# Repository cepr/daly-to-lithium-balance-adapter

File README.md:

# Energica Ego (2018) — Replacement Battery BMS Interface

Replacement traction battery for a 2018 Energica Ego. The original Lithium Balance s-BMS
master (BMCU) stays in the bike. The original cell-monitoring slave boards are gone, and a
small microcontroller board takes their place.

## Battery

| Item | Value |
|---|---|
| Chemistry | NMC |
| Modules | 4, connected in series |
| Cells per module | 20 in series |
| Total | **80S** |

## System overview

- **BMS master:** Lithium Balance s-BMS **BMCU** board (firmware 6.18.0, PIC18F4680).
- **Original slaves (LMUs):** 10 Lithium Balance cell-monitor boards with 8 cells each
  (10 × 8 = 80 cells). They are no longer available.
- **Replacement:** 4 **DALY Smart Active Balancers**: three 24S (the largest model) and one
  20S for the top module. They balance the cells and measure every cell voltage.
- **Interface board:** a microcontroller that reads the cell voltages from the 4 DALY
  balancers and answers the BMCU's slave-bus requests as if it were the 10 original LMUs.
  The BMCU keeps running its stock firmware and sees no difference.

### Balancer wiring and module overlap

A balancer covering only one module could balance cells within that module but not move
energy between modules. Balancers #1–#3 are therefore 24S: 20 channels on their own module and
4 on the next module up. A balancer that spans a module boundary moves charge across that
boundary, so all 4 modules are pulled to the same level. Module 4 is at the top of the pack and
has no next module, so balancer #4 is a 20S unit on module 4 only. The module 3/4 boundary is
bridged by balancer #3.

```
 Global cell       1–20     |    21–40    |    41–60    |    61–80
 Module          Module 1   |  Module 2   |  Module 3   |  Module 4
 Balancer #1   [  ch 1–20  ] [21–24]
 Balancer #2                 [  ch 1–20  ] [21–24]
 Balancer #3                               [  ch 1–20  ] [21–24]
 Balancer #4                                             [  ch 1–20  ]
```

| Balancer | Model | Channels 1–20 | Channels 21–24 (overlap) | Global cells |
|---|---|---|---|---|
| #1 | 24S | Module 1, cells 1–20 | Module 2, cells 1–4 | 1–24 |
| #2 | 24S | Module 2, cells 1–20 | Module 3, cells 1–4 | 21–44 |
| #3 | 24S | Module 3, cells 1–20 | Module 4, cells 1–4 | 41–64 |
| #4 | 20S | Module 4, cells 1–20 | — | 61–80 |

### Cell mapping

The BMCU numbers cells by slave: global cell = (slave − 1) × 8 + index + 1. Each cell is
read from the balancer that owns its module (the **primary** reading). Cells in an overlap
zone are measured by a second balancer too: each time the BMCU reads an LMU's cells, its
overlap cells switch between the two readings, so the BMCU and the diagnostic software see
both. The switch happens after the BMCU's temperature read, so the cells and temperatures of
one scan always come from the same balancer (primary first). A sense-wire or balancer fault shows as a cell whose value jumps between reads. A
missing reading is reported as a cell fault on its turn, even when the other one is valid.

| LMU (slave addr) | Global cells | Primary reading | Second reading |
|---|---|---|---|
| 1 | 1–8 | #1 ch 1–8 | — |
| 2 | 9–16 | #1 ch 9–16 | — |
| 3 | 17–24 | #1 ch 17–20 + #2 ch 1–4 | cells 21–24: #1 ch 21–24 |
| 4 | 25–32 | #2 ch 5–12 | — |
| 5 | 33–40 | #2 ch 13–20 | — |
| 6 | 41–48 | #3 ch 1–8 | cells 41–44: #2 ch 21–24 |
| 7 | 49–56 | #3 ch 9–16 | — |
| 8 | 57–64 | #3 ch 17–20 + #4 ch 1–4 | cells 61–64: #3 ch 21–24 |
| 9 | 65–72 | #4 ch 5–12 | — |
| 10 | 73–80 | #4 ch 13–20 | — |

### Temperature mapping

The interface board has 4 NTC inputs, one per module (T1 = module 1 … T4 = module 4), and each
DALY balancer reports its PCB temperature (balancer #n sits on module n). Each LMU fills its
four temperature registers like a real LMU (protocol doc §7.2):

| Register | Real LMU | Interface board |
|---|---|---|
| `0x7E5` | Pcb 1 | Balancer PCB temperature (DALY register `0x0020`) |
| `0x7E6` | Pcb 2 | Not fitted (`0x7A`) |
| `0x7E7` | Bat 1, NTC on L-J2 | Module NTC |
| `0x7E8` | Bat 2, optional NTC on L-J6 | Not fitted (`0x7A`) |

The BMCU ignores "not fitted" and uses the other two for its min/max/average. LMUs 3 and 8 span
a module boundary: like the overlap cells, each time the BMCU reads their temperatures they
switch between the two modules' values, in step with the overlap cells: upper module (#2 / #4,
the overlap cells' primary balancer) first, then the lower one. A fault shows on its own turn.

| LMU | Module(s) | Bat 1 (`0x7E7`) | Pcb 1 (`0x7E5`) |
|---|---|---|---|
| 1, 2 | 1 | T1 | Balancer #1 |
| 3 | 1 + 2 | T1, T2 in turn | #1, #2 in turn |
| 4, 5 | 2 | T2 | #2 |
| 6, 7 | 3 | T3 | #3 |
| 8 | 3 + 4 | T3, T4 in turn | #3, #4 in turn |
| 9, 10 | 4 | T4 | #4 |

A balancer that hasn't answered for 5 s reports its PCB sensor as open (`0xD7`), on top of
the cell faults.

Value coding (see [s-BMS protocol §7.2](LithiumBalance_sBMS_RS485_Protocol.md)):

- Valid readings are clamped to −40 … +120 °C, so they never collide with the special codes.
- An open sensor (ADC near full scale) reports `0xD7` (low-side fault). A shorted sensor (ADC near
  0) reports `0x79` (high-side fault). Every LMU that uses that sensor reports the fault.
- LMUs 3 and 8 report a fault if either of their two sensors is faulty, so a broken sensor
  can't be hidden by the average.

## Repository contents

| Path | Description |
|---|---|
| [`LithiumBalance_sBMS_RS485_Protocol.md`](LithiumBalance_sBMS_RS485_Protocol.md) | BMCU ↔ slave-board RS485 protocol, reverse-engineered from the BMCU firmware: framing, CRC, addressing, start-up enumeration, cyclic polling, register map, value coding. |
| [`DALY_Active_Balancer_UART_Protocol.md`](DALY_Active_Balancer_UART_Protocol.md) | DALY active balancer UART protocol (D2 "Modbus" framing, with the classic A5 framing as fallback), compiled from DALY documents and community work. Not yet validated on hardware; see its §8. |
| [`BMCU 6.18.0.hex`](BMCU%206.18.0.hex) | BMCU application firmware image, the source of the s-BMS protocol analysis. |
| [`pic18_dis.py`](pic18_dis.py) | Minimal PIC18 disassembler (PIC18F4680 SFR names) used to analyse the firmware: `python3 pic18_dis.py "BMCU 6.18.0.hex" > bmcu.asm` |
| [`slave_sim/`](slave_sim/) | Python/Tkinter simulator of up to 32 s-BMS slave boards, plus a BMCU emulator and tests. Use it to check the protocol against the real BMCU before the interface board exists. See [`slave_sim/README.md`](slave_sim/README.md). |
| [`can_monitor/`](can_monitor/) | Python/Tkinter Linux GUI (SocketCAN) that decodes the battery CAN messages in [`Battery_canbus_protocol.html`](Battery_canbus_protocol.html), with plotting, recording and log replay. See [`can_monitor/README.md`](can_monitor/README.md). |
| [`daly/`](daly/) | DALY balancer tooling. `fake_balancer.py` emulates a balancer (D2 protocol) on a USB-TTL adapter, for testing the firmware; see [Testing on the NUCLEO-G0B1RE](firmware/README.md#testing-on-the-nucleo-g0b1re). |
| [`docs/`](docs/) | Images used by this README (`system_overview.svg`). |
| [`hardware/interface_board/`](hardware/interface_board/) | KiCad 10 project of the interface board (draft): root sheet plus Power, MCU, BMCU (RS485), CAN, Temperatures, FANs, and one isolated balancer channel sheet used 4 times. PCB routed (first pass). Custom symbols are in `local.kicad_sym`, custom footprints in `lithium_balance.pretty` and `Molex.pretty`. |
| [`firmware/`](firmware/) | Interface board firmware in Rust (Embassy): s-BMS slave emulation, DALY polling, cell and temperature mapping. Compiles and is unit-tested on the PC; not yet run on hardware. See [`firmware/README.md`](firmware/README.md). |

## Protocol summary

| | s-BMS slave bus | DALY balancer |
|---|---|---|
| Physical | RS485, half-duplex, multi-drop | TTL UART (open-collector TX, needs pull-up) or RS485 |
| Format | 38400 baud, 8N1 | 9600 baud, 8N1 |
| Framing | ASCII hex: `CMD DEST SRC PAYLOAD CRC_H CRC_L CR` | Binary, 8-byte Modbus-like request (`0xD2` …) |
| CRC | CRC-16, poly 0xAC9A, init 0xFFFF (bytes 0x00/0x0D/0x1B bumped by 1) | CRC-16/Modbus |
| Role of the interface board | Slave (answers the BMCU) | Master (polls each balancer) |

On the s-BMS side the interface board has to:

1. Take part in the start-up enumeration. Each emulated LMU answers address `F0` in
   daisy-chain order and accepts its address `01`…`0A`.
2. Answer `q` reads of register `0x7D0` (8 cell voltages, uint16 big-endian, mV) and
   `0x7E5` (4 temperatures, int8 °C, see [Temperature mapping](#temperature-mapping)).
3. Keep the BMCU's charge counter: the BMCU writes it to registers `0x7E0`–`0x7E3` of slave 1
   every few seconds and reads it back at start-up to restore its SoC. The board must store it
   across power cycles (protocol doc §7.6).
4. Report missing or stale DALY data as a fault (for example `0x4000` for the affected cells, or no reply),
   so the BMCU's protection logic still works.
5. Build each LMU's 8 cells from the right balancer channels (see [Cell mapping](#cell-mapping)),
   and report the two readings of an overlap cell in turn.

See the two protocol documents for the details.

## Hardware

> **Status:** proposed parts, not yet prototyped. Check the datasheets and current availability before
> ordering.

### Isolation concept

Each balancer's comm port is referenced to the negative of the module it sits on, so the 4
ports are at very different potentials:

| Balancer | Port ground ≈ | Highest cell ≈ |
|---|---|---|
| #1 | 0 V | 100 V |
| #2 | 84 V | 185 V |
| #3 | 168 V | 270 V |
| #4 | 252 V | 336 V |

The interface board therefore talks to each balancer over its **TTL UART** through its **own
isolator**. That gives 4 separate isolated domains, each isolated from the 12 V side too. This
doesn't depend on whether DALY's RS485 port is isolated (unknown), and each balancer has its own
link, so they don't need different addresses. The BMCU side stays non-isolated, because the BMCU
shares the bike's 12 V / chassis ground.

```
12 V ─► protection ─► buck 5 V ─► LDO 3.3 V ─► MCU (STM32G0B1KBT6/KET6) ◄── 8 MHz oscillator
                                                │
            BMCU (J3) ◄── RS485 transceiver ◄───┤ USART2            (12 V / chassis domain)
                  CAN ◄── CAN transceiver   ◄───┤ FDCAN1
          4 × NTC ──► filter / clamp       ───►─┤ ADC1 ×4
              8 × fan ◄── Q2 driver        ◄────┤ TIM1_CH1 PWM 25 kHz
                                                │
                    USART1, 3, 5, 6 (one each) ─┴─► 4 × ISO7721 ─► DALY UART #1..#4
                                                    (balancer side powered by the DALY connector)
```

### Bill of materials

Each schematic symbol has `Manufacturer` and `MPN` fields, and a `DigiKey` field with the DigiKey
part number for cut-tape packaging (`…CT-ND`; parts not sold on tape, such as connectors, use
their plain `…-ND` number).

| Function | Qty | Part | Notes |
|---|---|---|---|
| MCU | 1 | **STM32G0B1KBT6** (LQFP-32, 0.8 mm pitch); alternate: **STM32G0B1KET6** | Cortex-M0+ 64 MHz, 128 KB flash, 144 KB RAM. In 32 pins it still has one USART per balancer (no multiplexer), a USART with hardware RS485 DE, FDCAN, enough ADC inputs and timers. See [Pin assignment](#pin-assignment). Develop on a NUCLEO-G0B1RE (same chip family). Use the plain KBT6/KET6, not the "…TxN" variants. The KET6 is the same chip and package with 512 KB flash (dual-bank): drop-in, the KB firmware runs on it unchanged. |
| Clock | 1 | X1, **Abracon ASE-8.000MHZ-LC-T** (8 MHz, 3.3 V CMOS output, ±50 ppm, −40…+85 °C, 3.2 × 2.5 mm) | Output to PC14 (OSC_IN); the firmware uses HSE bypass mode and the PLL to run at 64 MHz. The LQFP-32 has no OSC_OUT pin, so a passive crystal can't be used. Gives CAN the clock accuracy it needs (the internal HSI16 is only ±1 %). Pin 1 (enable) tied to 3.3 V. No capacitor of its own: C201 (100 nF), placed between X1 and the MCU's pin 4, decouples both. |
| MCU decoupling | 3 | C201 100 nF and C202 4.7 µF on VDD/VDDA (pin 4); C203 100 nF on NRST | |
| Status LED | 1 | D201 + R201 1 kΩ, on PB5 | |
| Balancer isolator | 4 | U601, U701, U801, U901: **TI ISO7721DWV** (wide-body SOIC-8, 5 kVrms reinforced) | 2 channels, one each way. Each side runs from 2.25–5.5 V, so it works whether the DALY supply is 3.3 V or 5 V. The balancer side is powered from the DALY UART connector. Equivalents: Si8621 (5 kV grade), ADuM1201. |
| MCU TX pull-up | 4 | R601, R701, R801, R901: 10 kΩ to 3.3 V | Holds each isolator input high (UART idle) while the MCU is in reset. |
| DALY TX pull-up | 4 | R603–R606: 10 kΩ to DALY VCC | DALY TX is open-collector. |
| Balancer-side decoupling | 4 | R602/R702/R802/R902 10 Ω in series on VCC, then C602/C702/C802/C902 100 nF + C603/C703/C803/C903 1 µF | Isolates the isolator from the long harness. Isolator side 1 has 100 nF (C601, C701, C801, C901). |
| BMCU RS485 transceiver | 1 | U301, **TI THVD1450** (3.3 V, ±18 kV ESD, SOIC-8) | Half duplex. DE driven by USART2's hardware DE output, /RE tied to DE. R301 10 kΩ pulls DE low (driver off during reset); R303 10 kΩ pulls RO high (RX idle while the receiver is off). More robust option: SN65HVD1781-Q1 (automotive, ±70 V fault protection; needs 5 V). |
| RS485 protection | 1 | D301, SM712 TVS on A/B | |
| RS485 termination | 1 | R302, 120 Ω, **fitted** | Remove it if the BMCU end already terminates the bus. The THVD1450 has built-in fail-safe, so there are no bias resistors. |
| CAN transceiver | 1 | U401, **MCP2562-E/SN** (SOIC-8) | 5 V supply, logic-side supply pin (VIO) on 3.3 V. R401 10 kΩ pulls STBY high. |
| CAN protection | 1 | D401, NUP2105L | ESD on CANH/CANL. |
| CAN termination | 1 | R402, R403 2 × 60.4 Ω + C403 4.7 nF split termination, **DNP** | Fit it only if this node is at the end of the bus. |
| NTC front end | 4 | R501/R503/R505/R507 10 kΩ 1 % pull-up to 3.3 V, R502/R504/R506/R508 1 kΩ series + C501–C504 100 nF to the ADC pin, D501–D504 BAV99 clamp | For 10 kΩ NTC sensors. The sensors must be insulated from the cells and rated for the pack voltage: these inputs are on the 12 V side. |
| Programming header | 1 | J11, 2×5 shrouded box header, 2.54 mm (IDC) | Pinout of the common ST-LINK/V2 clone USB dongle, so it connects with the dongle's 10-wire ribbon cable. See [Programming header](#programming-header). |
| Debug header | 1 | J202, 1×2 pin header, 2.54 mm: 1 TX (PC6), 2 GND | LPUART2 debug console, TX only. |
| Input fuse | 1 | F101, polyfuse 0.5 A hold, 30 V (1812) | Electronics only: the fans have their own input (see [Fans](#fans)). |
| Reverse-polarity protection | 1 | D102, SS34 Schottky (3 A, SMA), in series after the fuse | |
| Input TVS | 1 | D101, **SMBJ18A** (unidirectional, cathode on the fused 12 V), after the fuse | Load dump on the bike's 12 V. Clamps at about 29 V, against the R-78E's 28 V input rating (check its absolute maximum). Same part as D104. |
| Input decoupling | 2 | C101 10 µF 50 V (1210), C102 100 nF 50 V on +12 V | |
| Power LED | 1 | D103 (green) + R101 1 kΩ, on 3.3 V | |
| Fan power input | 1 | J18, Molex Mini-Fit Jr 2×3 right-angle, **0039301060** (5569-06A2, tin): 1, 4 GND; 2, 5 +12 V; 3, 6 not connected. 16 AWG wire | 8 A for 8 fans, 2 pins per polarity. Fused at the bike end with a 10 A blade fuse. Same part as the fan connectors. |
| Fan connectors | 4 | J14–J17, Molex Mini-Fit Jr 2×3 right-angle, **0039301060** (5569-06A2, tin) | Use tin-plated Mini-Fit Jr terminals in the harness. 2 fans per connector, see [Fans](#fans) for the pinout. The fans' own 4-pin plugs connect through a short adapter harness; their tach wire isn't used. |
| Fan fuses | 8 | F102–F109, **Bel Fuse 0ZCF0200AF2C** (polyfuse, 2.0 A hold, 4.0 A trip, 24 V, 2920) | One per fan, so one shorted or stalled fan can't take down the others. The 2.0 A hold keeps margin over the 1 A fan as the hold current drops at high ambient temperature. |
| Fan rail capacitors | 2 | C1, C2, **Panasonic EEE-FK1V470P** (47 µF 35 V electrolytic, 6.3 × 5.8 mm SMD, AEC-Q200, 240 mA ripple); alternate: **EEE-FK1V470AP** (same ratings and size) | In parallel (94 µF); two small cans instead of one 100 µF for layout. Near J18 / along the fan power trace, grounded to the fan ground path. They only see the fans' motor commutation current, so a general-purpose series (≥ 150 mA ripple each) is enough. The footprint is `CP_Elec_6.3x7.7`, whose pads are identical to `CP_Elec_6.3x5.8`, so the 5.8 mm-high can fits. |
| Fan input TVS | 1 | D104, **SMBJ18A** (unidirectional), cathode on +12 V | Clamps spikes on the fan rail, e.g. from unplugging the fans under 8 A, to about 29 V, below C1/C2's 35 V rating. That is above the fuses' 24 V rating, but only for the microseconds of a spike; a fuse only has the supply voltage across it once it has tripped, and 12 V is well within 24 V. |
| Fan PWM driver | 1 | Q2, **Nexperia 2N7002BKS** (dual N-MOSFET, SOT-363, Vgs(th) 2.1 V max) | See [Fans](#fans). Plus R202 100 Ω (gate series), R203 100 kΩ (gate pull-down) and R204/R205 10 kΩ (gate divider from the fan 12 V). |
| Fan ground link | 1 | R206, 0 Ω (0805), **DNP** | Joins `GNDPWR` to `GND` on the board. Not fitted: the grounds are joined in the harness, see [Fan ground](#fan-ground). |
| 5 V buck | 1 | U101, **Recom R-78E5.0-0.5** (7–28 V in, SIP3) | C103 10 µF and C104 1 µF on the output. The load is about 100 mA, mostly the CAN transceiver while it is transmitting. |
| 3.3 V LDO | 1 | U102, **TI TPS73633DBVR** (400 mA, SOT-23-5) | EN tied to VIN (always on). Pin 4 (NR) left open. Stable with any output capacitor; C105 1 µF on the output. The 3.3 V load is well under 100 mA. |

### Connectors

| Ref | Function | Part | Pinout |
|---|---|---|---|
| J3 | BMCU: 12 V supply and RS485 slave bus | Molex Mini-Fit Jr 2×2 (0015247040) | 1 GND, 2 +12 V in, 3 RS485 A, 4 RS485 B |
| J1, J2, J5, J6 | DALY UART, balancers #1, #2, #3, #4 (isolated) | JST-GH 6-pin, right-angle (SM06B-GHS-TB) | 1 to DALY RX (command), 2 from DALY TX (response), 3–4 not connected, 5 DALY VCC, 6 DALY GND (B−) |
| J13 | CAN | Molex Micro-Fit 3.0 2×2 right-angle (43045-0400) | 1 CANH, 2 CANL, 3–4 GND |
| J19–J22 | NTC T1–T4 | Molex Micro-Fit 3.0 2-pin right-angle (43045-0200) | 1 NTC, 2 GND |
| J18 | Fan power input | Molex Mini-Fit Jr 2×3 right-angle (0039301060) | 1, 4 GND; 2, 5 +12 V; 3, 6 not connected |
| J14–J17 | Fans, 2 per connector | Molex Mini-Fit Jr 2×3 right-angle (0039301060) | See [Fans](#fans) |
| J11 | Programming (SWD) | 2×5 IDC box header, 2.54 mm | See [Programming header](#programming-header) |
| J202 | Debug console | 1×2 pin header, 2.54 mm | 1 TX (PC6), 2 GND |

The BMCU sheet also holds a drawing of the BMCU board (U1) and its connector J4 (Mini-Fit, 0015286042), for the 3D view only: neither is in the BOM nor fitted on the board.

### Pin assignment

As wired in the schematic (`mcu.kicad_sch`), checked against the `STM32G0B1KBTx` symbol in the
KiCad library. Check it again in STM32CubeMX.

| Function | Peripheral | Pins (LQFP-32 pin no.) |
|---|---|---|
| BMCU RS485 | USART2 TX / RX / DE (hardware driver enable) | PA2 (9), PA3 (10), PA1 (8) |
| Balancer #1 | USART1 TX / RX | PB6 (30), PB7 (31) |
| Balancer #2 | USART5 TX / RX | PB3 (27), PB4 (28) |
| Balancer #3 | USART3 TX / RX | PB2 (17), PB0 (15) |
| Balancer #4 | USART6 TX / RX | PA4 (11), PA5 (12) |
| CAN | FDCAN1 RX / TX, transceiver STBY | PB8 (32), PB9 (1), PA15 (26) |
| Temperatures 1–4 | ADC1_IN0, IN6, IN7, IN9 | PA0 (7), PA6 (13), PA7 (14), PB1 (16) |
| Fan PWM | TIM1_CH1 | PA8 (18) |
| Debug console (TX only) | LPUART2_TX | PC6 (20) |
| Programming | SWDIO / SWCLK / NRST | PA13 (24), PA14 (25), PF2-NRST (6) |
| Clock input | HSE (OSC_IN, bypass), from the 8 MHz oscillator | PC14 (2) |
| Status LED | GPIO | PB5 (29) |
| Spare | GPIO | PC15 (3), PA9 (19), PA10 (21), PA11 (22), PA12 (23) |

### Programming header

J11 is a 2×5, 2.54 mm shrouded box header with the pinout of the cheap **ST-LINK/V2 clone USB
dongles**: the aluminium USB-stick ST-LINKs. This is the clones' own pinout, not an ST or ARM standard. The
dongle's 10-wire IDC ribbon cable plugs straight in.

| Pin | Dongle signal | Board | |
|---|---|---|---|
| 1 | RST | NRST (PF2-NRST, pin 6) | |
| 2 | SWCLK | PA14 (pin 25) | |
| 3 | SWIM | not connected | STM8 only |
| 4 | SWDIO | PA13 (pin 24) | |
| 5, 6 | GND | GND | |
| 7, 8 | 3.3 V output | **not connected** | |
| 9, 10 | 5.0 V output | **not connected** | |

The dongle's 3.3 V and 5 V pins are supply *outputs* from the PC's USB port. They stay
unconnected: wired to the board's 12 V input they would back-feed the PC, and wired to the 5 V rail they would
fight the R-78E. Power the board from its own 12 V input while programming. There is no
target-voltage sense on this pinout; the dongle assumes 3.3 V, which matches the board.

A Nucleo's on-board ST-LINK can also be used, through jumper wires from its SWD header (CN4):
see [`firmware/README.md`](firmware/README.md#using-a-nucleos-st-link-for-the-interface-board).

PA9/PA10 are left unused because they also carry the USB-C dead-battery pull-downs, which are active
at reset. STBY has a pull-up, so the CAN transceiver stays in standby until the firmware enables it.

**Alternatives considered:**
- **STM32G031F8P6** (TSSOP-20): no CAN, and too few pins for the analog inputs and PWM.
- **STM32F042K6T6** (LQFP-32, with CAN): only 2 USARTs, so the 4 balancers would have to share
  one UART through a 74HC4052 multiplexer on the 3.3 V side. It's also an older family.

### Fans

8 standard 4-wire PC fans (12 V, 1 A each), all driven by one PWM signal. The tach outputs are
not used. The fans stop when their PWM line is grounded, and the board holds them stopped
while the MCU is in reset.

Q2 is a 2N7002BKS: two N-MOSFETs in one package. Q2A (pins 1 S, 2 G, 6 D) is driven by the
MCU. Q2B (pins 4 S, 5 G, 3 D) grounds the fans' PWM line.

```
 12V_FAN ── R204 10k ──┬── R205 10k ── GND
                       │
                       ├── Q2B gate (5)     Q2B drain (3) ──► PWM pins of J14–J17
                       │                    Q2B source (4) ─► GND
                       └── Q2A drain (6)
 PA8 ── R202 100R ──┬── Q2A gate (2)        Q2A source (1) ─► GND
                    └── R203 100k ── GND
```

| State | PA8 | Q2A | Q2B | Fans |
|---|---|---|---|---|
| MCU in reset or unprogrammed | floating (R203 pulls the gate low) | off | on | **stopped** |
| Board 3.3 V missing, fan 12 V present | 0 V | off | on | **stopped** |
| Running, PWM high | 3.3 V | on | off | line floats high (the fan pulls it up internally): run |
| Running, PWM low | 0 V | off | on | line grounded: stop |

So the PWM duty cycle at PA8 is the fan speed: 0 % stops the fans, 100 % is full speed.

- **Q2B's gate** comes from the R204/R205 divider on the fan 12 V: about 6 V normally, and about
  15 V at the TVS clamp voltage. That's within the 2N7002's ±20 V gate rating. Q2B only has to sink the fans'
  pull-up current, at most about 5 mA per fan, 40 mA in total.
- **Fan power** doesn't go through the electronics' 12 V input. It has its own input (J18), a TVS
  (D104), 2 × 47 µF capacitors (C1, C2) and a polyfuse per fan. 8 A needs about 6 mm of trace width
  on 1 oz copper (about 10 °C rise), a copper pour, or 2 oz copper. The fan ground is its own net
  (`GNDPWR`) and returns to J18 on its own path. Q2, R203 and R205 are on `GNDPWR` too. See
  [Fan ground](#fan-ground).
- **Fan input J18** (Mini-Fit Jr 2×3, same part as the fan connectors): pins 1 and 4 GND, pins 2 and 5
  +12 V, pins 3 and 6 not connected.
- **Fan connectors J14–J17:** Mini-Fit Jr 2×3, 2 fans each (1 A per pin, well within the
  Mini-Fit Jr rating). Each fan's +12 V comes through its own polyfuse.

  | Pin | Signal | Pin | Signal |
  |---|---|---|---|
  | 1 | Fan A GND | 4 | Fan B GND |
  | 2 | Fan A +12 V | 5 | Fan B +12 V |
  | 3 | Fan A PWM | 6 | Fan B PWM |

  Adapter harness to each fan's 4-pin plug: GND → fan pin 1, +12 V → fan pin 2, PWM → fan pin 4;
  fan pin 3 (tach) is left open.
- **Bike supply:** 8 fans draw about 100 W continuously, more at start-up. Check that the Ego's
  12 V DC/DC converter can supply that on top of the bike's own loads.
- **Firmware:** 25 kHz (the 4-wire fan spec allows 21–28 kHz). Speed follows the hottest module
  temperature, and a faulty sensor runs the fans at full speed. See
  [`firmware/README.md`](firmware/README.md#fans).

#### Fan ground

The fan ground (`GNDPWR`, J18 pins 1/4) and the logic ground (`GND`, J3 pin 1) are **joined in
the harness, not on the board**, so the fans' 8 A return current never flows through the board's
signal ground (MCU, ADC, RS485 and CAN reference).

- **Where to join them:** at the bike's ground point, not at the BMCU. J3's GND is also the BMCU's
  ground and the RS485 reference; joining the fan ground there would send the fan current through
  it.
- **Q2A gate drive** is the only signal that crosses the two grounds: PA8 is referenced to `GND`,
  Q2A's source to `GNDPWR`. At the board, `GNDPWR` sits above `GND` by the drop on the fan return
  wire, about 0.25 V at 8 A for 1.5 m of 16 AWG plus contacts (about 0.5 V at start-up). Q2A then gets
  2.8–3.0 V of gate drive. Q2 (2N7002BKS) has Vgs(th) at most 2.1 V and Q2A only sinks about
  1.2 mA, so that's enough with some margin. Keep the fan ground wire short and heavy; for more
  margin, fit a dual N-MOSFET with Vgs(th) ≤ 1.5 V in the same SOT-363 footprint.
- **Broken wire:** with the fan ground open, the fans stop and `GNDPWR` floats towards 12 V; the
  only path to the logic side is R203 + R202 into PA8 (under 0.1 mA into its protection diode). With
  the logic ground open, the board loses its supply return. Neither damages anything.
- **Fallback:** R206 (0 Ω, DNP), near J18, joins the two grounds on the board. Fit it only if the
  harness join causes trouble; the fan ground wire must then still go back to the bike ground.

### PCB layout

2-layer board, 160 × 100 mm. Target: at least 6–8 mm creepage across each isolation barrier, a
slot under each isolator, and the 4 isolated domains kept apart from each other as well (#1 and #4
are about 250 V apart; balancer #4's domain is up to about 336 V from the 12 V side).

As routed (first pass):

- **Slots:** a 4.5 × 10.6 mm routed slot (Edge.Cuts) runs under each isolator (U601, U701, U801,
  U901), along the barrier.
- **Clearance, isolated domain to the 12 V side** (copper to copper, either layer): balancer #1
  8.05 mm, #2 8.05 mm, #3 7.43 mm, #4 7.93 mm. The closest points are `GND_BAL` to `GND` tracks.
- **Clearance between isolated domains:** at least 12.9 mm.

**Isolator fallback:** if the DALY connector supply turns out to be unusable: **TI ISOW7821**, a 2-channel
isolator with a built-in isolated DC/DC converter, fed from 5 V on the board side (about 70–100 mA
each). It has a different footprint and needs the 5 V rail at each isolator, so it means a board
revision.

### DALY UART connector checklist

The UART connector also powers the DALY Bluetooth dongle, so it should provide a supply
(probably 5 V). Check each balancer before you rely on it:

- [ ] **Pinout and voltage:** measure VCC against the connector GND with the balancer powered from
  its cells. Note which pins the Bluetooth dongle uses.
- [ ] **Load capability:** load VCC with about 10 mA (470 Ω at 5 V, 330 Ω at 3.3 V) and check that
  it doesn't sag.
- [ ] **Sleep behaviour:** check whether VCC stays on when the balancer sleeps. Either way, set the
  sleep time to 65535 (disabled), see [DALY protocol §1](DALY_Active_Balancer_UART_Protocol.md).
- [ ] **GND reference:** confirm the connector GND is the balancer's B− (cell 0).
- [ ] **RS485 isolation (for information):** measure the voltage and resistance between the RS485
  port's GND (or A/B) and B−. A few ohms or the same potential means not isolated. MΩ with no
  voltage suggests isolated, but that still doesn't tell you the voltage rating.

### Open points

- **Fan ground:** check on the bike that the fans run at the commanded speed with the grounds
  joined in the harness (Q2A gate margin, see [Fan ground](#fan-ground)).
- **Input TVS vs buck:** D101 (SMBJ18A) clamps a load dump at about 29 V, just above the R-78E's
  28 V input rating. Check the R-78E's absolute maximum input voltage.
- **ERC:** 2 errors and 11 warnings are left: J1 pins 3/4 without no-connect flags, two dangling
  wire stubs at the CANH/CANL labels on the CAN sheet, J6 pin 4 off-grid, X1 and GND symbols out
  of date with the library, and Q2's pins of type "unspecified".
- **DRC:** clean except one schematic-parity warning: the BMCU outline footprint U1 (3D view only)
  is on the board while its symbol is marked "not on board". The silkscreen checks are set to
  "ignore" in the board setup; turn them back on for a last check before ordering.
- **CAN:** not used yet. The 8 MHz oscillator is fitted for it (FDCAN can be clocked straight from it). Before connecting it to the bike's bus, find out the bitrate and which
  IDs are in use, and keep the node silent (listen-only) until then.
- **Standby drain:** each isolator draws a few mA from its module through the balancer's
  regulator, well under 2 Ah per month. Keeping the balancer awake already costs more than that.
  For long storage, switch off the interface board's 12 V with the bike, so the balancers can
  sleep.

## Quick start (simulator)

```sh
pip install pyserial
python3 -m slave_sim.gui                          # GUI: emulate 10 slaves on a USB-RS485 adapter
python3 -m unittest slave_sim.test_protocol       # protocol unit tests
python3 -m slave_sim.fake_master --selftest       # BMCU emulator <-> simulator over a pty
```

## Status

- [x] s-BMS slave-bus protocol reverse-engineered from the BMCU firmware
- [x] Slave-board simulator and BMCU emulator
- [x] DALY balancer protocol reference compiled
- [ ] DALY protocol validated on a real balancer
- [ ] Inter-module balancing through the overlap verified
- [ ] DALY UART connector checked (see [checklist](#daly-uart-connector-checklist))
- [x] Interface board schematic drafted ([`hardware/interface_board/`](hardware/interface_board/))
- [x] Interface board PCB routed (first pass)
- [ ] Interface board schematic and PCB reviewed
- [x] Interface board firmware skeleton ([`firmware/`](firmware/)): compiles, logic unit-tested
- [ ] Firmware tested against the BMCU emulator and the real BMCU
- [ ] Test in the bike

## Safety

This is a high-voltage traction battery (80S NMC, about 300 V nominal). The BMCU makes its protection
decisions from the data this project feeds it. Wrong or stale cell voltages can hide an
over-charge or over-discharge. Validate everything on the bench before using it in the
vehicle.

Each balancer's sense harness spans a module boundary. If the pack has a service disconnect,
fuse or contactor between modules, the overlap wires bypass it. Fuse every sense lead at the
cell end, and remember that the harness can still be live when the modules are separated.

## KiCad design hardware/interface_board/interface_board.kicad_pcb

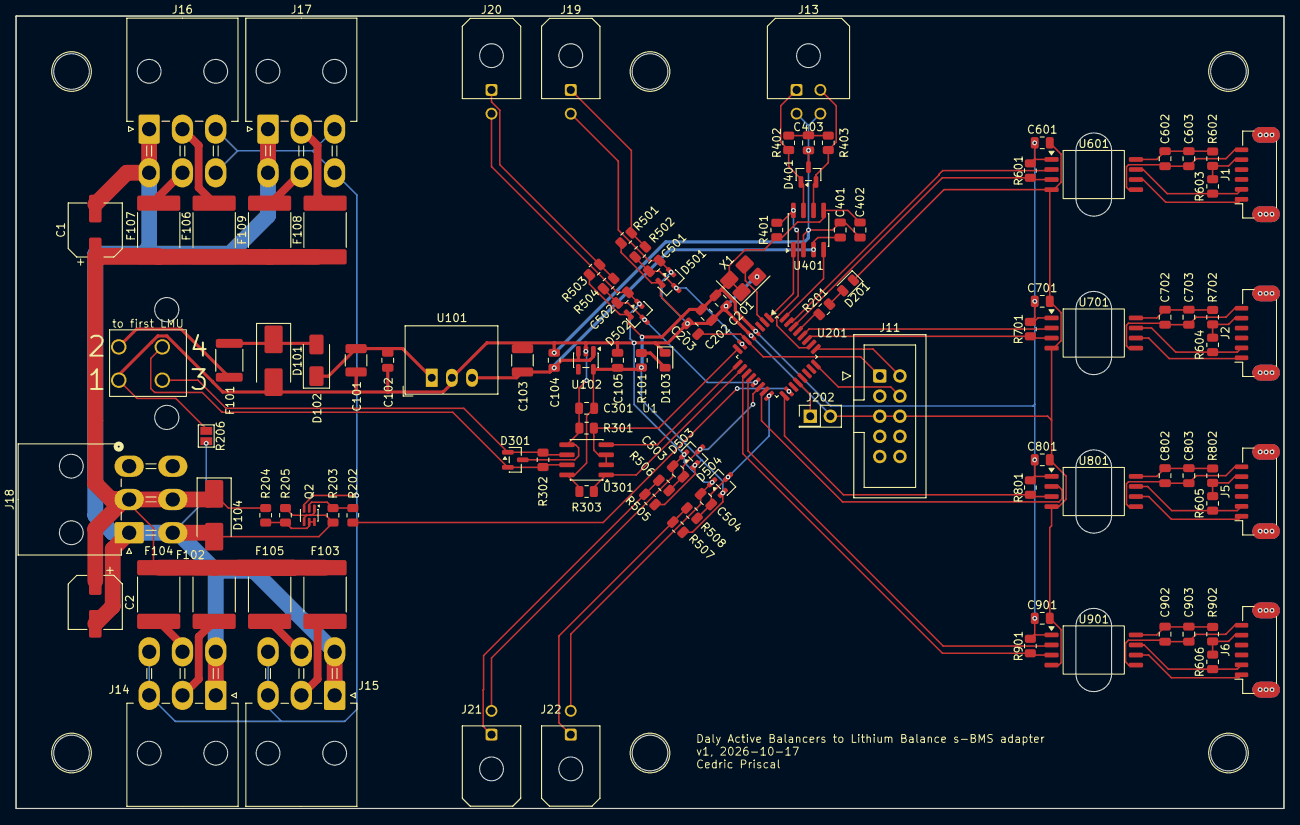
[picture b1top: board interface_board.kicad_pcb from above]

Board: 2 copper layers, 160.0 x 100.0 mm, 112 parts (1 on the bottom side), 75 nets.

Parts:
C1, C2: 47uF / 35V; CP_Elec_6.3x5.8
C101: 10uF 50V; C_1210_3225Metric
C102: 100nF 50V; C_0805_2012Metric
C103: 10uF 16V; C_1210_3225Metric
C104, C105, C603, C703, C803, C903: 1uF; C_0805_2012Metric
C201, C203, C301, C401, C402, C501, C502, C503, C504, C601, C602, C701, C702, C801, C802, C901, C902: 100nF; C_0805_2012Metric
C202: 4.7uF; C_0805_2012Metric
C403: 4.7nF; C_0805_2012Metric
D101, D104: SMBJ18A; D_SMB_Handsoldering
D102: SS34; D_SMA
D103: green; LED_0805_2012Metric
D201: status; LED_0805_2012Metric
D301: SM712; SOT-23
D401: NUP2105L; SOT-23
D501, D502, D503, D504: BAV99; SOT-23
F101: 0.5A hold, 30V; Fuse_1812_4532Metric
F102, F103, F104, F105, F106, F107, F108, F109: 2.0A hold, 4.0A trip, 24V; Fuse_2920_7451Metric
J1, J2, J5, J6: JST-GH; JST_GH_SM06B-GHS-TB_1x06-1MP_P1.25mm_Horizontal
J3: Molex 0015247040; Molex_0015247040
J11: ST-LINK/V2 clone USB dongle; IDC-Header_2x05_P2.54mm_Vertical
J13: Molex 430450400; Molex_Micro-Fit_3.0_43045-0400_2x02_P3.00mm_Horizontal
J14, J15, J16, J17, J18: Molex 0039301060; Molex_Mini-Fit_Jr_5569-06A2_2x03_P4.20mm_Horizontal
J19, J20, J21, J22: Molex 430450202; Molex_Micro-Fit_3.0_43045-0200_2x01_P3.00mm_Horizontal
J202: DEBUG TX; PinHeader_2x01_P2.54mm_Vertical
Q2: 2N7002BKS; SOT-363_SC-70-6
R101, R201, R502, R504, R506, R508: 1k; R_0805_2012Metric
R202: 100; R_0805_2012Metric
R203: 100k; R_0805_2012Metric
R204, R205, R301, R303, R401, R601, R603, R604, R605, R606, R701, R801, R901: 10k; R_0805_2012Metric
R206: 0; SolderJumper-2_P1.3mm_Open_Pad1.0x1.5mm
R302: 120; R_0805_2012Metric
R402, R403: 60.4; R_0805_2012Metric
R501, R503, R505, R507: 10k 1%; R_0805_2012Metric
R602, R702, R802, R902: 10; R_0805_2012Metric
U1: BMCU
U101: R-78E5.0-0.5; Converter_DCDC_RECOM_R-78E-0.5_THT
U102: TPS73633DBVR; SOT-23-5
U201: STM32G0B1KET6; LQFP-32_7x7mm_P0.8mm
U301: THVD1450D; SOIC-8_3.9x4.9mm_P1.27mm
U401: MCP2562-E/SN; SOIC-8_3.9x4.9mm_P1.27mm
U601, U701, U801, U901: ISO7721DWV; SOIC-8_7.5x5.85mm_P1.27mm
X1: ASE-8.000MHZ-LC-T; Oscillator_SMD_Abracon_ASE-4Pin_3.2x2.5mm_HandSoldering

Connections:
12V_IN: F101.1, J3.2
+3V3: C105.1, C201.1, C202.1, C301.1, C402.1, C601.1, C701.1, C801.1, C901.1, D501.2 (A), D502.2 (A), D503.2 (A), D504.2 (A), R101.1, R303.1, R401.1, R501.1, R503.1, R505.1, R507.1, R601.1, R701.1, R801.1, R901.1, U102.5 (VOUT), U201.4 (VDD), U301.8 (VCC), U401.5 (Vio), U601.1 (VCC1), U701.1 (VCC1), U801.1 (VCC1), U901.1 (VCC1), X1.1 (EN), X1.4 (Vdd)
+5V: C103.1, C104.1, C401.1, U101.3 (OUT), U102.1 (VIN), U102.3 (EN), U401.3 (VDD)
+12V: C101.1, C102.1, D102.1 (K), U101.1 (IN)
/BMCU/RS485_A: D301.1 (A1), J3.3, R302.1, U301.6 (A)
/BMCU/RS485_B: D301.2 (A2), J3.4, R302.2, U301.7 (B)
/Balancer 1/DALY_UART_COMMAND: J1.1, U601.6 (OUTB)
/Balancer 1/DALY_UART_RESPONSE: J1.2, R603.1, U601.7 (INA)
/Balancer 1/DALY_VCC: J1.5, R602.1, R603.2
/Balancer 1/GND_BAL: C602.2, C603.2, J1.6, U601.5 (GND2)
/Balancer 1/VBAL: C602.1, C603.1, R602.2, U601.8 (VCC2)
/Balancer 2/DALY_UART_COMMAND: J2.1, U701.6 (OUTB)
/Balancer 2/DALY_UART_RESPONSE: J2.2, R604.1, U701.7 (INA)
/Balancer 2/DALY_VCC: J2.5, R604.2, R702.1
/Balancer 2/GND_BAL: C702.2, C703.2, J2.6, U701.5 (GND2)
/Balancer 2/VBAL: C702.1, C703.1, R702.2, U701.8 (VCC2)
/Balancer 3/DALY_UART_COMMAND: J5.1, U801.6 (OUTB)
/Balancer 3/DALY_UART_RESPONSE: J5.2, R605.1, U801.7 (INA)
/Balancer 3/DALY_VCC: J5.5, R605.2, R802.1
/Balancer 3/GND_BAL: C802.2, C803.2, J5.6, U801.5 (GND2)
/Balancer 3/VBAL: C802.1, C803.1, R802.2, U801.8 (VCC2)
/Balancer 4/DALY_UART_COMMAND: J6.1, U901.6 (OUTB)
/Balancer 4/DALY_UART_RESPONSE: J6.2, R606.1, U901.7 (INA)
/Balancer 4/DALY_VCC: J6.5, R606.2, R902.1
/Balancer 4/GND_BAL: C902.2, C903.2, J6.6, U901.5 (GND2)
/Balancer 4/VBAL: C902.1, C903.1, R902.2, U901.8 (VCC2)
/CAN/CANH: D401.1 (K), J13.1, R402.1, U401.7 (CANH)
/CAN/CANL: D401.2 (K), J13.2, R403.2, U401.6 (CANL)
/CAN/CAN_SPLIT: C403.1, R402.2, R403.1
/FANs/12V_FAN: C1.1, C2.1, D104.1 (K), F102.1, F103.1, F104.2, F105.2, F106.1, F107.2, F108.1, F109.2, J18.2, J18.5, R204.2
/FANs/PWM_OUT: J14.3, J14.6, J15.3, J15.6, J16.3, J16.6, J17.3, J17.6, Q2.3
/MCU/DBG_TX: J202.1, U201.20 (PC6)
/MCU/LED_A: D201.2 (A), R201.2
/MCU/LED_STATUS: R201.1, U201.29 (PB5)
/MCU/NRST: C203.1, J11.1, U201.6 (PF2)
/MCU/SWCLK: J11.2, U201.25 (SYS_SWCLK)
/MCU/SWDIO: J11.4, U201.24 (SYS_SWDIO)
/Power/12V_FUSED: D101.1 (K), D102.2 (A), F101.2
/Temperatures/NTC1: J19.1, R501.2, R502.1
/Temperatures/NTC2: J20.1, R503.2, R504.1
/Temperatures/NTC3: J21.1, R505.2, R506.1
/Temperatures/NTC4: J22.1, R507.2, R508.1
BAL1_RX: U201.31 (USART1_RX), U601.2 (OUTA)
BAL1_TX: R601.2, U201.30 (USART1_TX), U601.3 (INB)
BAL2_RX: U201.28 (USART5_RX), U701.2 (OUTA)
BAL2_TX: R701.2, U201.27 (USART5_TX), U701.3 (INB)
BAL3_RX: U201.15 (USART3_RX), U801.2 (OUTA)
BAL3_TX: R801.2, U201.17 (USART3_TX), U801.3 (INB)
BAL4_RX: U201.12 (USART6_RX), U901.2 (OUTA)
BAL4_TX: R901.2, U201.11 (USART6_TX), U901.3 (INB)
BMCU_DE: R301.1, U201.8 (USART2_DE), U301.2 (~RE), U301.3 (DE)
BMCU_RX: R303.2, U201.10 (USART2_RX), U301.1 (RO)
BMCU_TX: U201.9 (USART2_TX), U301.4 (DI)
CAN_RX: U201.32 (FDCAN1_RX), U401.4 (RXD)
CAN_STBY: R401.2, U201.26 (PA15), U401.8 (STBY)
CAN_TX: U201.1 (FDCAN1_TX), U401.1 (TXD)
FAN_PWM: R202.1, U201.18 (TIM1_CH1)
GND: C101.2, C102.2, C103.2, C104.2, C105.2, C201.2, C202.2, C203.2, C301.2, C401.2, C402.2, C403.2, C501.2, C502.2, C503.2, C504.2, C601.2, C701.2, C801.2, C901.2, D101.2 (A), D103.1 (K), D201.1 (K), D301.3 (common), D401.3 (A), D501.1 (K), D502.1 (K), D503.1 (K), D504.1 (K), J3.1, J11.5, J11.6, J13.3, J13.4, J19.2, J20.2, J21.2, J22.2, J202.2, R206.1, R301.2, U101.2 (GND), U102.2 (GND), U201.5 (VSS), U301.5 (GND), U401.2 (VSS), U601.4 (GND1), U701.4 (GND1), U801.4 (GND1), U901.4 (GND1), X1.2 (GND)
GNDPWR: C1.2, C2.2, D104.2 (A), J14.1, J14.4, J15.1, J15.4, J16.1, J16.4, J17.1, J17.4, J18.1, J18.4, Q2.1, Q2.4, R203.1, R205.1, R206.2
unnamed: D103.2 (A), R101.2
unnamed: F102.2, J14.2
unnamed: F104.1, J14.5
unnamed: F103.2, J15.2
unnamed: F105.1, J15.5
unnamed: F106.2, J16.2
unnamed: F107.1, J16.5
unnamed: F108.2, J17.2
unnamed: F109.1, J17.5
unnamed: Q2.2, R202.2, R203.2
unnamed: Q2.5, Q2.6, R204.1, R205.2
unnamed: U201.2 (RCC_OSC_IN), X1.3 (OUT)
TEMP1: C501.1, D501.3 (K), R502.2, U201.7 (ADC1_IN0)
TEMP2: C502.1, D502.3 (K), R504.2, U201.13 (ADC1_IN6)
TEMP3: C503.1, D503.3 (K), R506.2, U201.14 (ADC1_IN7)
TEMP4: C504.1, D504.3 (K), R508.2, U201.16 (ADC1_IN9)
